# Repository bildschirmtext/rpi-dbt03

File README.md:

# rpi-dbt03
Hardware, Software and Firmware for a Raspberry Pi to DBT-03 adapter

There is now a possibility to directly patch a Bookworm Raspbian image.

Run `./patch_image.sh <imagename>` as root. It only works on uncompressed images. You can then `dd` that image onto your SD-card or use the Raspberry Pi Imager. The later also allows you to set settings.
The image will reboot multiple times.

The boot partition can also hold a `btx_config.txt` file where you can configure the host to connect to.

```
BTX_HOST=btx.clarke-3.de
BTX_PORT=20000
```

## Old way of installing it

On the Raspberry PI check out this repository. 

Install the packages in install-packages.sh (run it as root). 

Enable spi with raspi-config. 

Change the baudrate of the programmer "linuxspi" to a smaller value 40000 is OK. This setting is found in /etc/avrdude.conf

This currently is still incomplete.

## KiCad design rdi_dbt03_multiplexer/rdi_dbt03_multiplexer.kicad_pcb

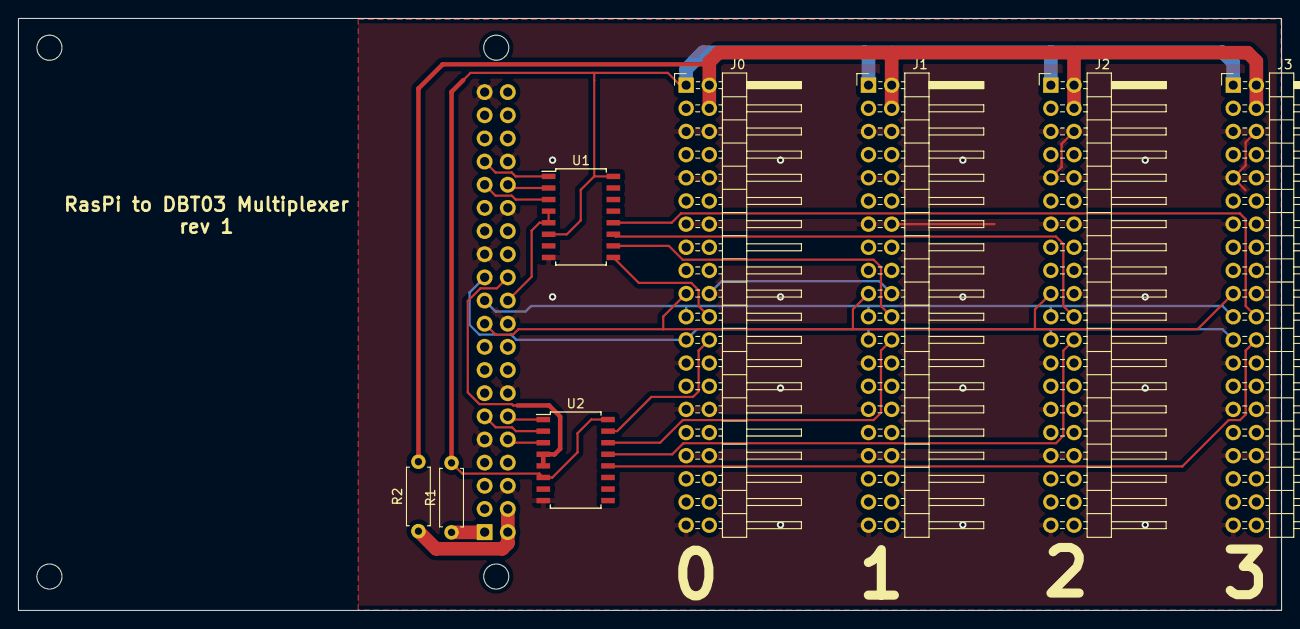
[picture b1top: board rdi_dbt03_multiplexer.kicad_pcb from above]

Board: 2 copper layers, 138.5 x 64.9 mm, 9 parts (1 on the bottom side), 24 nets.

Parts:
J0, J1, J2, J3: Conn_02x20_Odd_Even; Pin_Header_Angled_2x20_Pitch2.54mm
R1, R2: 0r; R_Axial_DIN0207_L6.3mm_D2.5mm_P7.62mm_Horizontal
RP1: Raspberry_Pi_2_3; raspberrypi_2_3
U1, U2: 74LS138; SOIC-16W_5.3x10.2mm_Pitch1.27mm

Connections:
/A0: RP1.12, U2.1
/A1: RP1.11, U2.2
/A2: RP1.10, U2.3
/B0: RP1.33, U1.1
/B1: RP1.32, U1.2
/B2: RP1.31, U1.3
/E5V: J0.2, J0.4, J1.2, J1.4, J2.2, J2.4, J3.2, J3.4, R2.2
/MISO: J0.21, J1.21, J2.21, J3.21, RP1.21
/MOSI: J0.19, J1.19, J2.19, J3.19, RP1.19
/RST_N: RP1.22, U1.4, U1.5
/RST_N0: J0.22, U1.9
/RST_N1: J1.22, U1.10
/RST_N2: J2.22, U1.11
/RST_N3: J3.22, U1.12
/SCK: J0.23, J1.23, J2.23, J3.23, RP1.23
/SPI_CS: RP1.24, U2.4, U2.5
/SPI_CS0: J0.24, U2.15
/SPI_CS1: J1.24, U2.14
/SPI_CS2: J2.24, U2.13
/SPI_CS3: J3.24, U2.12
GND: J0.5, J0.6, J0.9, J0.10, J0.13, J0.14, J0.20, J0.25, J0.29, J0.30, J0.33, J0.34, J0.39, J1.5, J1.6, J1.9, J1.10, J1.13, J1.14, J1.20, J1.25, J1.29, J1.30, J1.33, J1.34, J1.39, J2.5, J2.6, J2.9, J2.10, J2.13, J2.14, J2.20, J2.25, J2.29, J2.30, J2.33, J2.34, J2.39, J3.5, J3.6, J3.9, J3.10, J3.13, J3.14, J3.20, J3.25, J3.29, J3.30, J3.33, J3.34, J3.39, RP1.6, RP1.9, RP1.14, RP1.20, RP1.25, RP1.30, RP1.34, RP1.39, U1.8, U2.8
unnamed: R1.1, RP1.1
unnamed: R2.1, RP1.2, RP1.4
VCC: J0.1, J1.1, J2.1, J3.1, R1.2, U1.6, U1.16, U2.6, U2.16

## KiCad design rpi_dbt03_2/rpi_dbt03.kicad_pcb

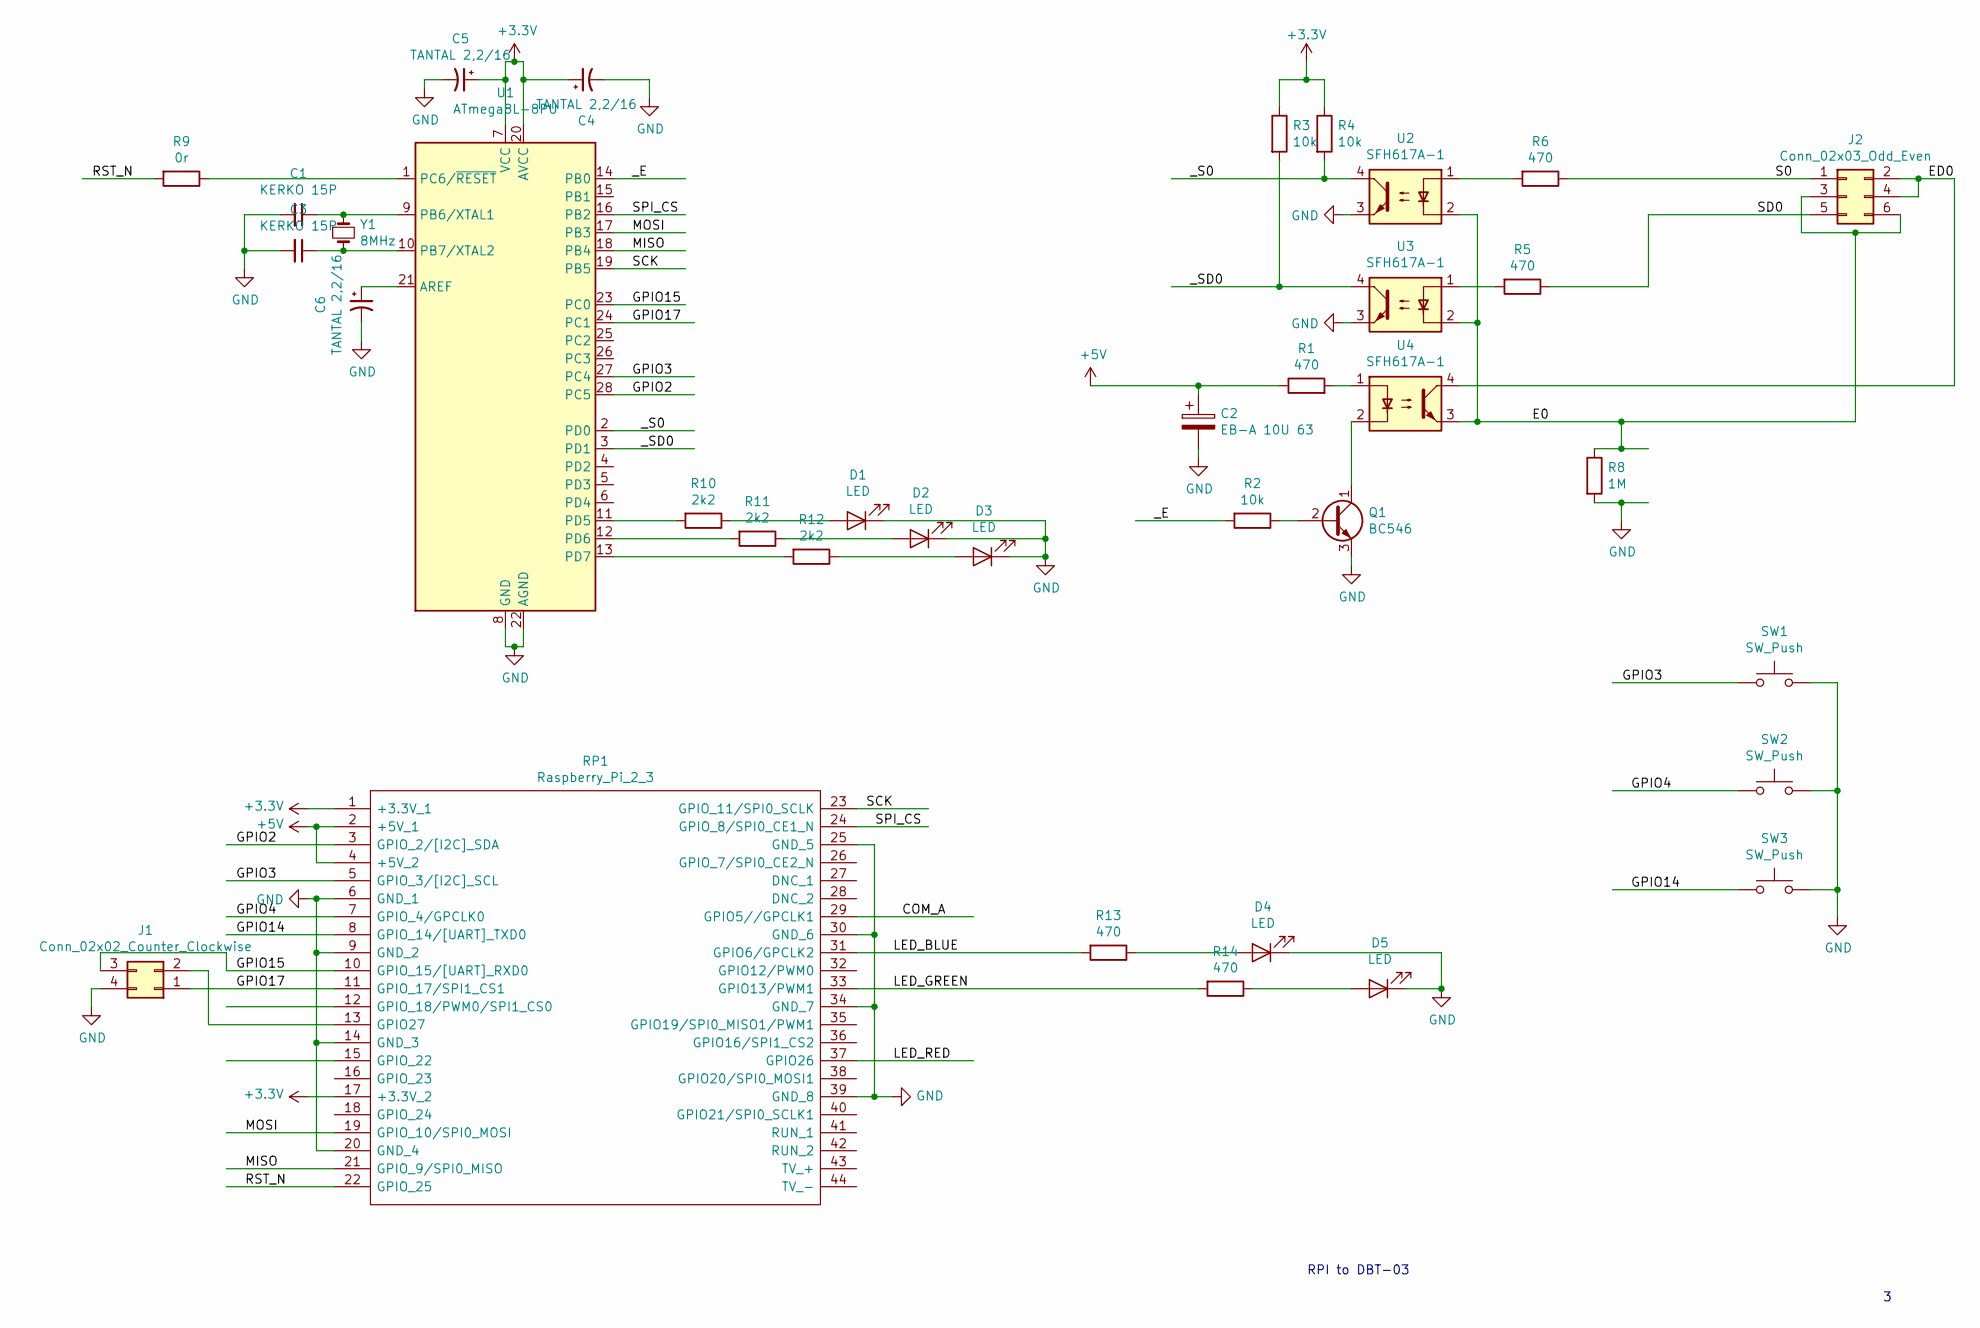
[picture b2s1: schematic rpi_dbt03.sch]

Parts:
C1, C3: KERKO 15P; C_Disc_D3.0mm_W1.6mm_P2.50mm
C2: EB-A 10U 63; CP_Radial_D5.0mm_P2.50mm
C4, C5: TANTAL 2,2/16; CP_Radial_Tantal_D4.5mm_P2.50mm
C6: TANTAL 2,2/16; C_Disc_D3.0mm_W2.0mm_P2.50mm
D1, D2, D3, D4, D5: LED; LED_D3.0mm
J1: Conn_02x02_Counter_Clockwise; Pin_Header_Straight_2x02_Pitch2.54mm
J2: Conn_02x03_Odd_Even; Pin_Header_Straight_2x03_Pitch2.54mm
Q1: BC546; TO-92_Inline_Wide
R1, R5, R6, R13, R14: 470; R_Axial_DIN0207_L6.3mm_D2.5mm_P7.62mm_Horizontal
R2, R3, R4: 10k; R_Axial_DIN0207_L6.3mm_D2.5mm_P7.62mm_Horizontal
R8: 1M; R_Axial_DIN0207_L6.3mm_D2.5mm_P7.62mm_Horizontal
R9: 0r; R_Axial_DIN0207_L6.3mm_D2.5mm_P7.62mm_Horizontal
R10, R11, R12: 2k2; R_Axial_DIN0207_L6.3mm_D2.5mm_P7.62mm_Horizontal
RP1: Raspberry_Pi_2_3; raspberrypi_2_3; Manufacturer_Part_Number Raspberry Pi 2 or 3
SW1, SW2, SW3: SW_Push; SW_PUSH_6mm
U1: ATmega8L-8PU; DIP-28_W7.62mm
U2, U3, U4: SFH617A-1; DIP-4_W7.62mm_Socket_LongPads
Y1: 8MHz; Crystal_HC49-4H_Vertical

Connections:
+3V3: C4.1, C5.1, R3.1, R4.1, RP1.1 (+3.3V_1), RP1.17 (+3.3V_2), U1.7 (VCC), U1.20 (AVCC)
+5V: C2.1, R1.1, RP1.2 (+5V_1), RP1.4 (+5V_2)
/E0: J2.3, J2.6, R8.1, U2.2, U3.2, U4.3
/ED0: J2.2, J2.4, U4.4
/GPIO2: RP1.3 (GPIO_2/[I2C]_SDA), U1.28 (PC5)
/GPIO3: RP1.5 (GPIO_3/[I2C]_SCL), SW1.1, U1.27 (PC4)
/GPIO4: RP1.7 (GPIO_4/GPCLK0), SW2.1
/GPIO14: RP1.8 (GPIO_14/[UART]_TXD0), SW3.1
/GPIO15: J1.3, RP1.10 (GPIO_15/[UART]_RXD0), U1.23 (PC0)
/GPIO17: J1.1, RP1.11 (GPIO_17/SPI1_CS1), U1.24 (PC1)
/LED_BLUE: R13.2, RP1.31 (GPIO6/GPCLK2)
/LED_GREEN: R14.2, RP1.33 (GPIO13/PWM1)
/MISO: RP1.21 (GPIO_9/SPI0_MISO), U1.18 (PB4)
/MOSI: RP1.19 (GPIO_10/SPI0_MOSI), U1.17 (PB3)
/RST_N: R9.2, RP1.22 (GPIO_25)
/S0: J2.1, R6.1
/SCK: RP1.23 (GPIO_11/SPI0_SCLK), U1.19 (PB5)
/SD0: J2.5, R5.1
/SPI_CS: RP1.24 (GPIO_8/SPI0_CE1_N), U1.16 (PB2)
/_E: R2.2, U1.14 (PB0)
/_S0: R4.2, U1.2 (PD0), U2.4
/_SD0: R3.2, U1.3 (PD1), U3.4
GND: C1.2, C2.2, C3.2, C4.2, C5.2, C6.2, D1.1 (K), D2.1 (K), D3.1 (K), D4.1 (K), D5.1 (K), J1.4, Q1.3 (E), R8.2, RP1.6 (GND_1), RP1.9 (GND_2), RP1.14 (GND_3), RP1.20 (GND_4), RP1.25 (GND_5), RP1.30 (GND_6), RP1.34 (GND_7), RP1.39 (GND_8), SW1.2, SW2.2, SW3.2, U1.8 (GND), U1.22 (AGND), U2.3, U3.3
unnamed: C1.1, U1.9 (PB6/XTAL1), Y1.1
unnamed: C3.1, U1.10 (PB7/XTAL2), Y1.2
unnamed: C6.1, U1.21 (AREF)
unnamed: D1.2 (A), R10.1
unnamed: D2.2 (A), R11.1
unnamed: D3.2 (A), R12.1
unnamed: D4.2 (A), R13.1
unnamed: D5.2 (A), R14.1
unnamed: J1.2, RP1.13 (GPIO27)
unnamed: Q1.1 (C), U4.2
unnamed: Q1.2 (B), R2.1
unnamed: R1.2, U4.1
unnamed: R5.2, U3.1
unnamed: R6.2, U2.1
unnamed: R9.1, U1.1 (PC6/~RESET)
unnamed: R10.2, U1.11 (PD5)
unnamed: R11.2, U1.12 (PD6)
unnamed: R12.2, U1.13 (PD7)

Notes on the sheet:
RPI to DBT-03

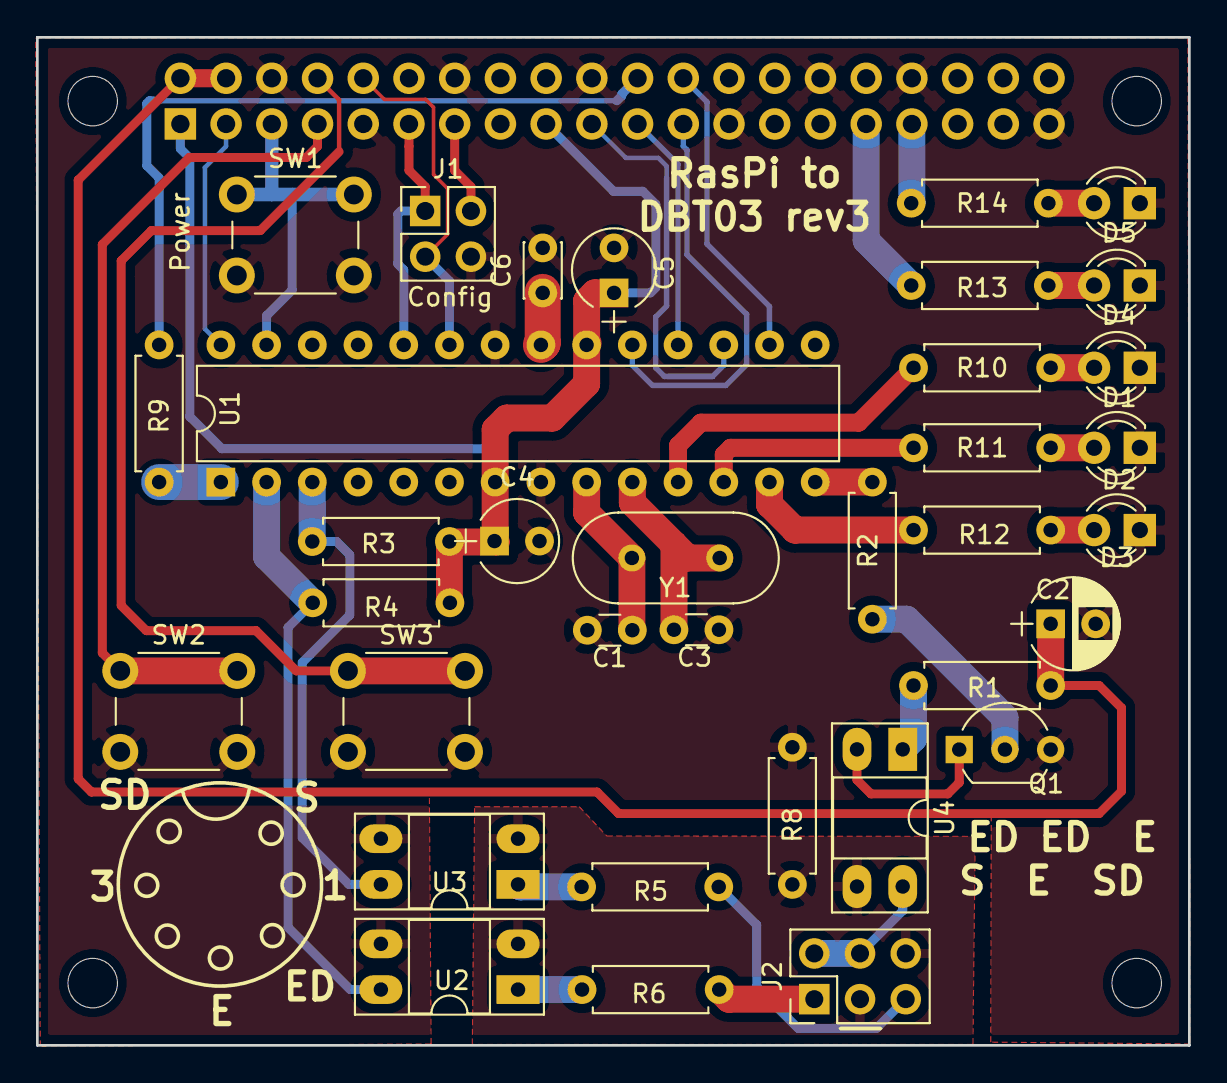
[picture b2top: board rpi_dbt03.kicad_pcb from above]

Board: 2 copper layers, 64.0 x 56.0 mm, 36 parts (0 on the bottom side), 41 nets.

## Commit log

2020-02-16 Added some documentation about the various protocols spoken in this project.
2020-02-21 It now compiles and installs on the ATMega 8
2020-02-22 Get SPI-Communication and LEDs running. Please make sure to patch your hardware to the new revision that is coming up.
2020-02-22 Found a hardware Bug. Pin 18 of the ATMega8 needs to connected to Pin 24 of the Raspberry PI. This will mean that a new layout is needed, however so far you can patch it by adding one bodge wire.
2020-02-24 Added SPI_CE line and swapped incorrectly named _SD0 and _S0 netw
2020-02-26 First "release" of the SPI protocoll
2020-02-29 First Version that kinda works.
2020-02-29 Minor change, I think 2 network names have been swapped
2020-02-29 More usability thanks to do_everything.sh
2020-02-29 Added enabling the service.
2020-03-02 Fixed the frequencies according to official documentation
2020-06-20 Version 3 which adds 3 buttons and some configuration jumpers
2020-10-08 Added patched avrdude.conf to program mikrocontroller even when in internal RC oscillator
2020-10-08 Minor cleanups to chase the warnings away
2020-10-08 Irgendwas
2021-06-02 Multiplexerplatine
2023-12-17 Moved to BCM 2832 library for accessing GPIOs
2024-09-24 Update rpi_dbt03.c
    Support optional /boot/btx_ip.txt file
2024-09-29 Add binary and boot config line
2024-10-03 Script to patch a raspbian OS image
2024-10-03 Enabled domain lookup
2024-10-03 New wrapper for service
2024-10-03 updated patch_image.sh to support new way of patching an SD-card
2024-10-03 Documented config file
